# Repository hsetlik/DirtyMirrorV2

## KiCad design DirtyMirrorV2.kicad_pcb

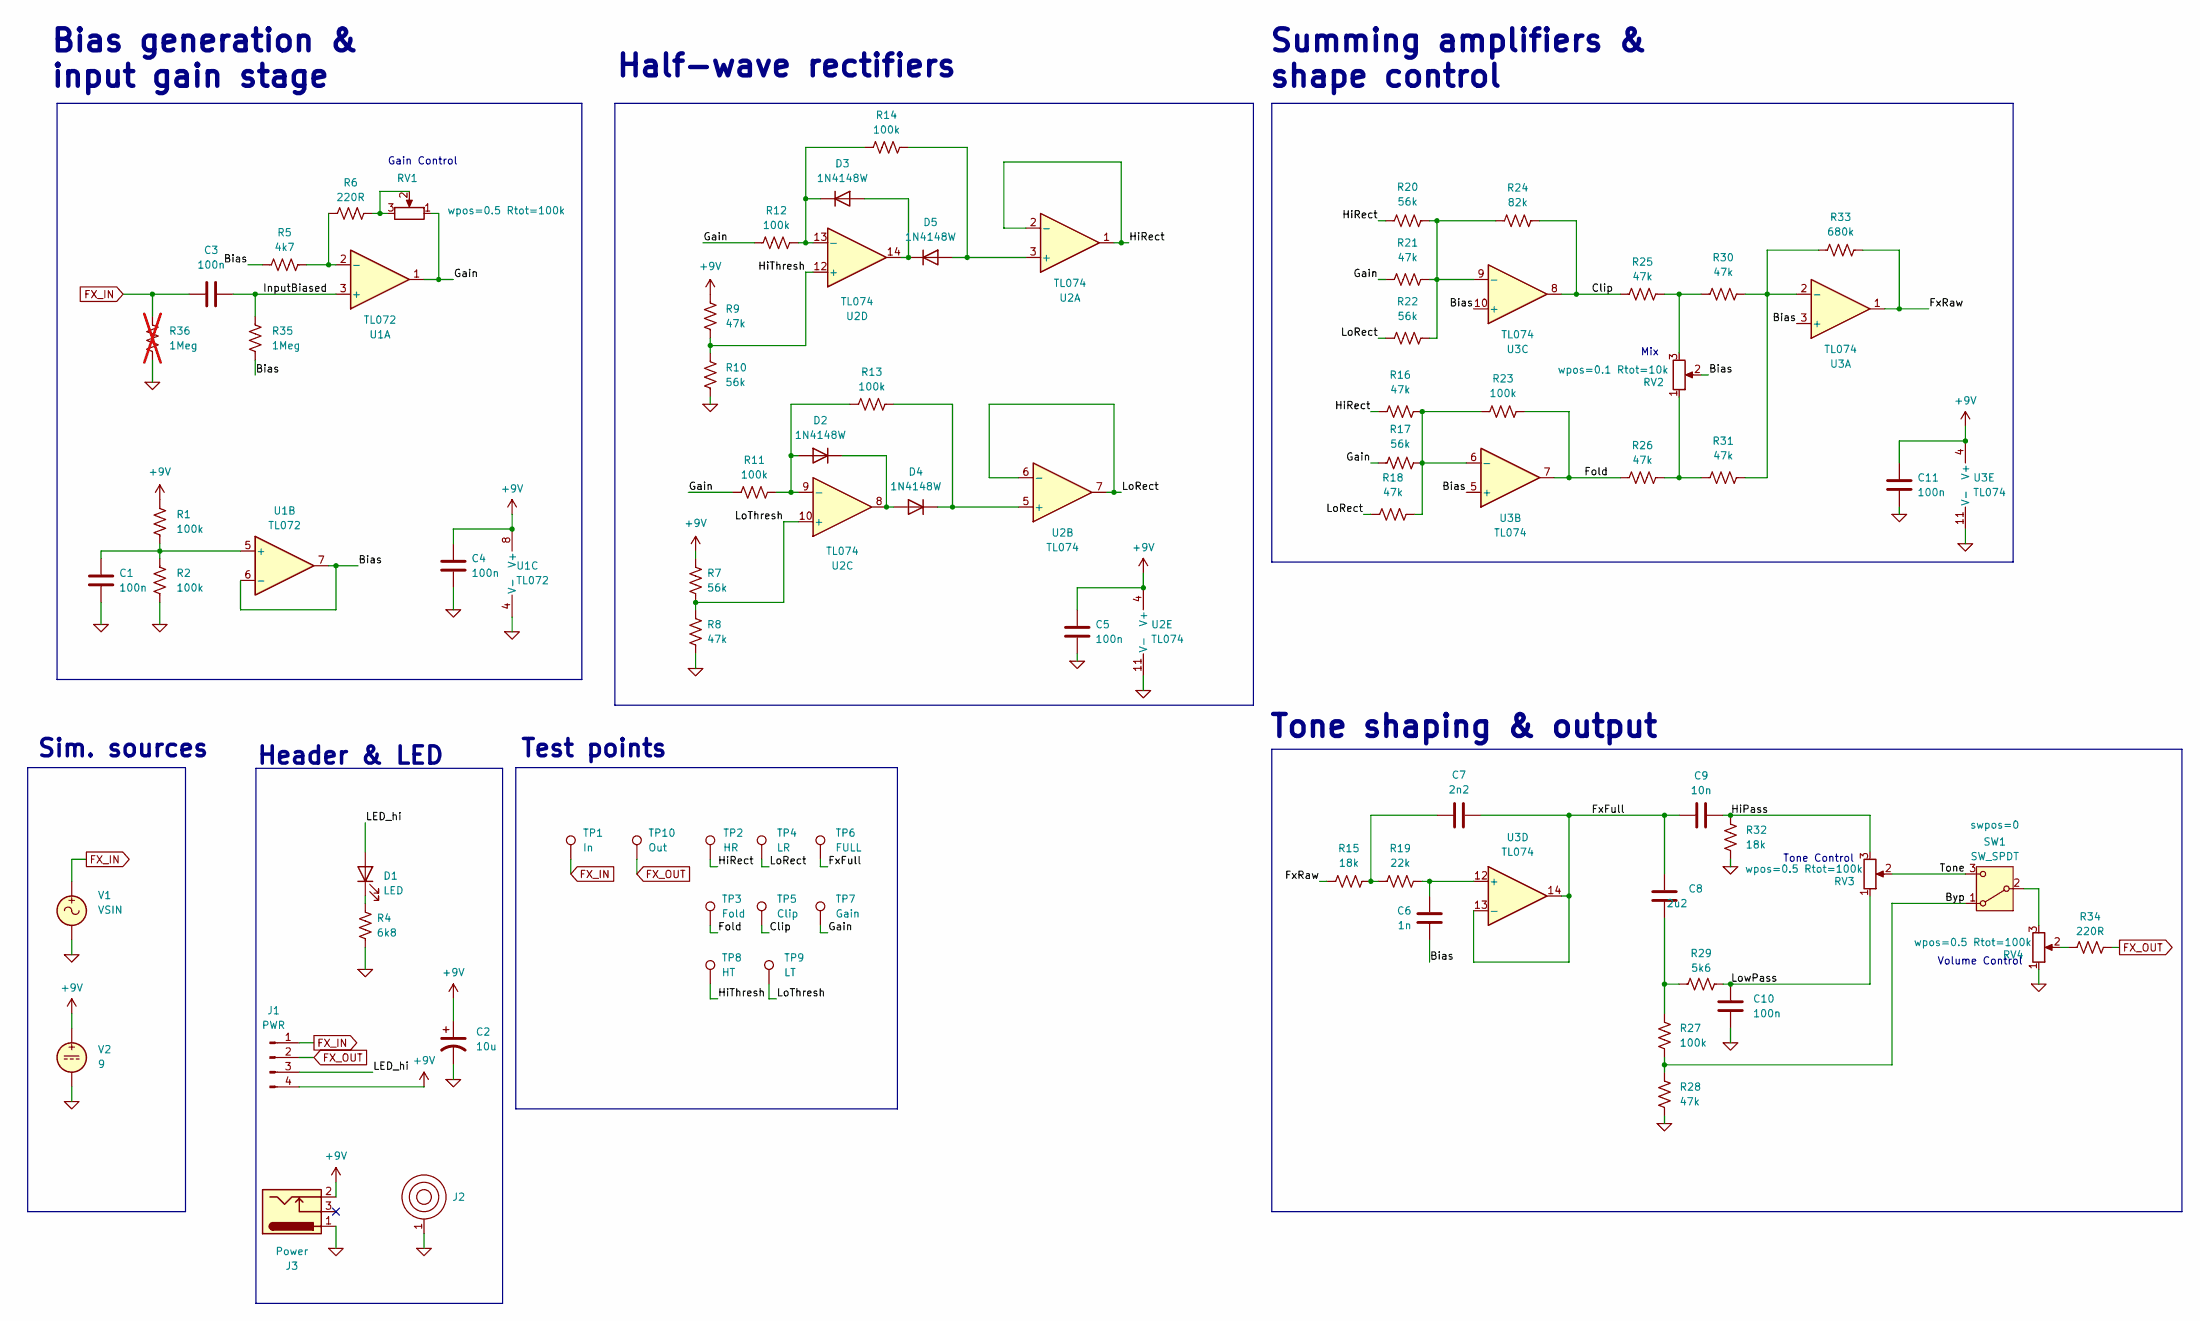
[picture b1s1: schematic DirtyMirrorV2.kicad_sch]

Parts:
C1, C3, C4, C5, C10, C11: 100n; C_0805_2012Metric
C2: 10u; CP_Radial_D5.0mm_P2.50mm
C6: 1n; C_0805_2012Metric
C7: 2n2; C_0805_2012Metric
C8: 2u2; C_0805_2012Metric
C9: 10n; C_0805_2012Metric
D1: LED; LED_D3.0mm
D2, D3, D4, D5: 1N4148W; D_SOD-123
J1: PWR; PinHeader_1x04_P2.54mm_Vertical
J2: BatteryContact_Keystone_243
J3: Power; BarrelJack_Horizontal
R1, R2, R11, R12, R13, R14, R23, R27: 100k; R_0805_2012Metric
R4: 6k8; R_0805_2012Metric
R5: 4k7; R_0805_2012Metric
R6, R34: 220R; R_0805_2012Metric
R7, R10, R17, R20, R22: 56k; R_0805_2012Metric
R8, R9, R16, R18, R21, R25, R26, R28, R30, R31: 47k; R_0805_2012Metric
R15, R32: 18k; R_0805_2012Metric
R19: 22k; R_0805_2012Metric
R24: 82k; R_0805_2012Metric
R29: 5k6; R_0805_2012Metric
R33: 680k; R_0805_2012Metric
R35: 1Meg; R_0805_2012Metric
R36: 1Meg; R_0805_2012Metric; not fitted
RV1, RV2, RV3, RV4: R_Potentiometer; Potentiometer_Alpha_RV16AF_42_Single_Long
SW1: SW_SPDT; SW_SPDT_Dailywell_Mini_1M
TP1: In; TestPoint_THTPad_D2.0mm_Drill1.0mm_VAL
TP2: HR; TestPoint_THTPad_D2.0mm_Drill1.0mm_VAL
TP3: Fold; TestPoint_THTPad_D2.0mm_Drill1.0mm_VAL
TP4: LR; TestPoint_THTPad_D2.0mm_Drill1.0mm_VAL
TP5: Clip; TestPoint_THTPad_D2.0mm_Drill1.0mm_VAL
TP6: FULL; TestPoint_THTPad_D2.0mm_Drill1.0mm_VAL
TP7: Gain; TestPoint_THTPad_D2.0mm_Drill1.0mm_VAL
TP8: HT; TestPoint_THTPad_D2.0mm_Drill1.0mm_VAL
TP9: LT; TestPoint_THTPad_D2.0mm_Drill1.0mm_VAL
TP10: Out; TestPoint_THTPad_D2.0mm_Drill1.0mm_VAL
U1: TL072; SOIC-8_3.9x4.9mm_P1.27mm
U2, U3: TL074; SOIC-14_3.9x8.7mm_P1.27mm
V1: VSIN
V2: 9

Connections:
0: C1.2, C2.2, C4.2, C5.2, C10.2, C11.2, J2.1, J3.1, R2.2, R4.2, R8.2, R10.2, R28.2, R32.2, R36.2, RV4.1, U1.4 (V-), U2.11 (V-), U3.11 (V-), V1.2, V2.2
+9V: C2.1, C4.1, C5.1, C11.1, J1.4, J3.2, R1.1, R7.1, R9.1, U1.8 (V+), U2.4 (V+), U3.4 (V+), V2.1
/Bias: C6.2, R5.1, R35.2, RV2.2, U1.6 (-), U1.7, U3.3 (+), U3.5 (+), U3.10 (+)
/Byp: R27.2, R28.1, SW1.1 (A)
/Clip: R24.2, R25.1, TP5.1 (1_1), U3.8
/Fold: R23.2, R26.1, TP3.1 (1_1), U3.7
/FxFull: C7.2, C8.1, C9.1, TP6.1 (1_1), U3.13 (-), U3.14
/FxRaw: R15.1, R33.2, U3.1
/Gain: R11.1, R12.1, R17.1, R21.1, RV1.1, TP7.1 (1_1), U1.1
/HiPass: C9.2, R32.1, RV3.3
/HiRect: R16.1, R20.1, TP2.1 (1_1), U2.1, U2.2 (-)
/HiThresh: R9.2, R10.1, TP8.1 (1_1), U2.12 (+)
/InputBiased: C3.2, R35.1, U1.3 (+)
/LED_hi: D1.2 (A), J1.3
/LoRect: R18.1, R22.1, TP4.1 (1_1), U2.6 (-), U2.7
/LoThresh: R7.2, R8.1, TP9.1 (1_1), U2.10 (+)
/LowPass: C10.1, R29.2, RV3.1
/Tone: RV3.2, SW1.3 (C)
FX_IN: C3.1, J1.1, R36.1, TP1.1 (1_1), V1.1
FX_OUT: J1.2, R34.2, TP10.1 (1_1)
unnamed: C7.1, R15.2, R19.1
unnamed: C8.2, R27.1, R29.1
unnamed: D1.1 (K), R4.1
unnamed: D2.2 (A), R11.2, R13.1, U2.9 (-)
unnamed: D2.1 (K), D4.2 (A), U2.8
unnamed: D3.2 (A), D5.1 (K), U2.14
unnamed: D3.1 (K), R12.2, R14.1, U2.13 (-)
unnamed: D4.1 (K), R13.2, U2.5 (+)
unnamed: D5.2 (A), R14.2, U2.3 (+)
unnamed: R6.2, RV1.2, RV1.3
unnamed: R25.2, R30.1, RV2.3
unnamed: R26.2, R31.1, RV2.1
unnamed: R34.1, RV4.2
unnamed: RV4.3, SW1.2 (B)
unnamed: R5.2, R6.1, U1.2 (-)
unnamed: C1.1, R1.2, R2.1, U1.5 (+)
unnamed: R30.2, R31.2, R33.1, U3.2 (-)
unnamed: R16.2, R17.2, R18.2, R23.1, U3.6 (-)
unnamed: R20.2, R21.2, R22.2, R24.1, U3.9 (-)
unnamed: C6.1, R19.2, U3.12 (+)

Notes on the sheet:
Test points
Gain Control
Sim. sources
Header & LED
Tone Control
Summing amplifiers & shape control
Mix
Bias generation & input gain stage
Volume Control
Half-wave rectifiers
Tone shaping & output

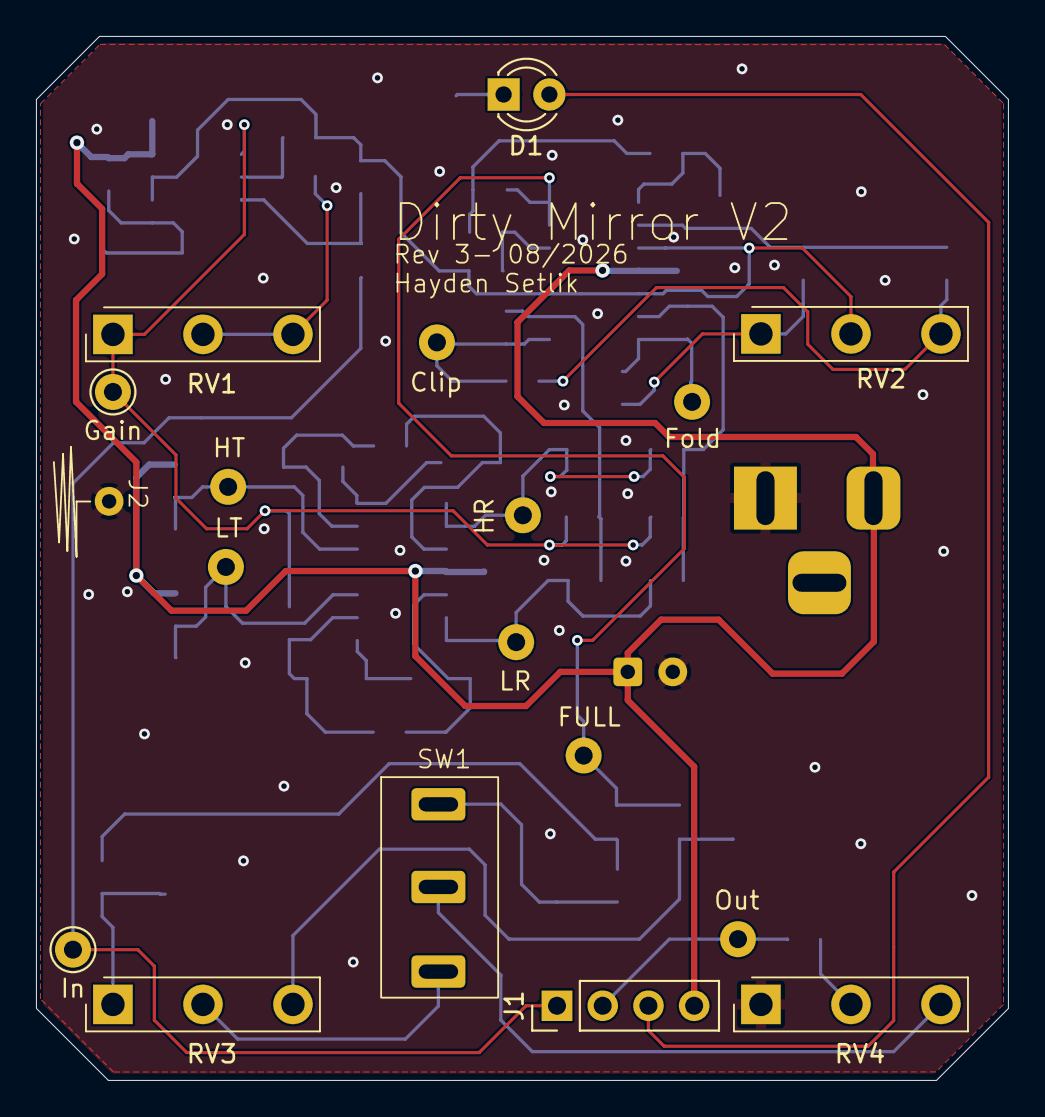
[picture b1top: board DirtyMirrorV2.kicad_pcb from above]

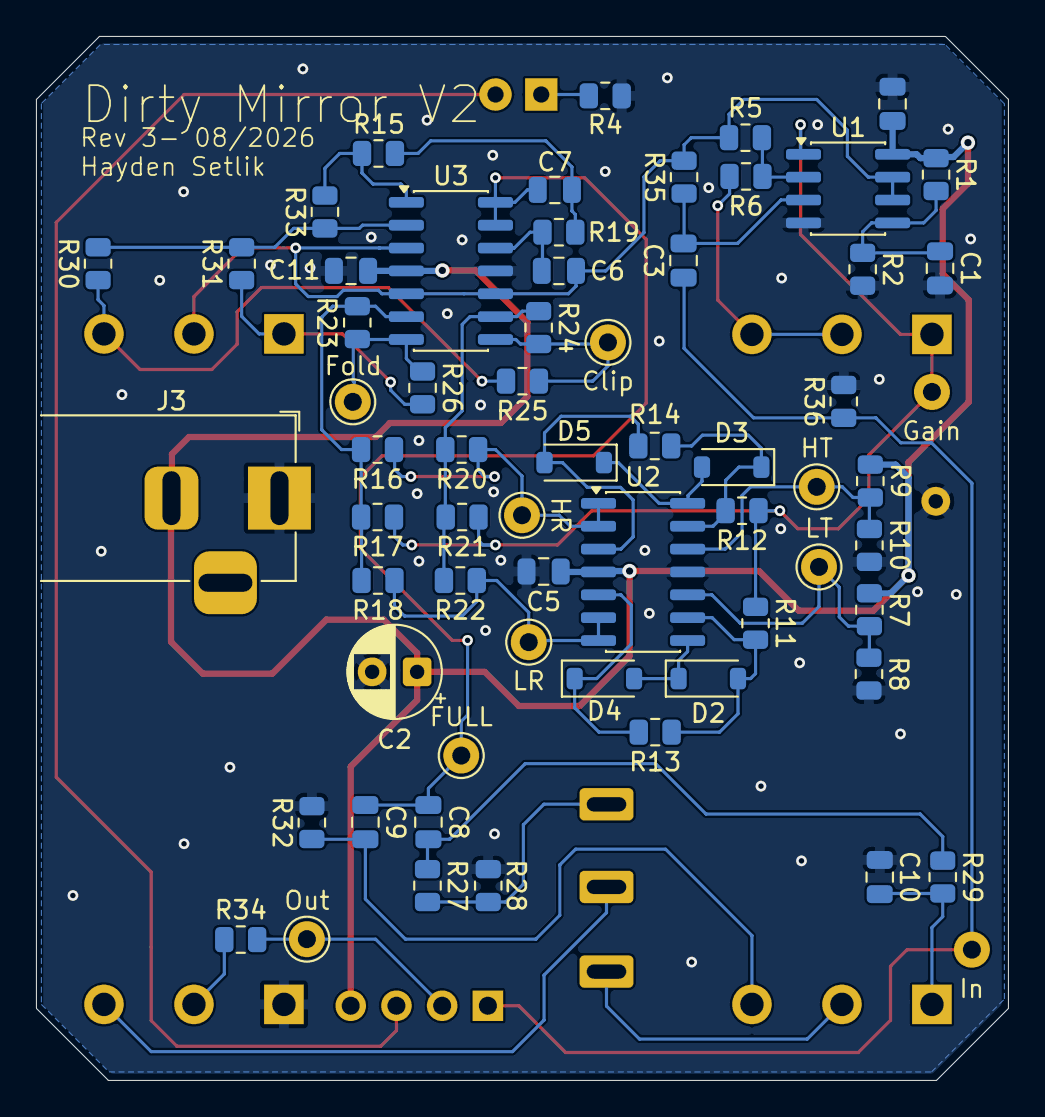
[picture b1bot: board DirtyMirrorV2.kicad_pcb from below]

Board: 2 copper layers, 54.0 x 58.0 mm, 72 parts (62 on the bottom side), 40 nets.

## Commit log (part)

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2026-01-28 simulation working, schem labeled
2026-01-28 footprints assigned
2026-01-29 board routed, DRC passing
2026-01-29 switched to routed power
2026-01-30 elbow room
2026-01-30 top jacks, new routing
2026-02-14 rev1 gerbers ready
2026-02-14 sike minor fix. DRC passing
2026-02-14 rev1 sent to fab
2026-02-28 value tweaks, added BOM
2026-03-01 minor tweaks after sound testing
2026-06-06 resistor values tweaked to taste
2026-06-07 higher output gain
2026-06-09 changed tone ctrl high pass
2026-06-09 added tone stack simulation
2026-06-11 switched tone bypass voltage divider
2026-06-11 de-hissing butterworth changes
